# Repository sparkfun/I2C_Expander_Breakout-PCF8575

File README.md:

SparkFun I2C Expander Breakout - PCF8575
========================================

[*SparkFun I2C Expander Breakout - PCF8575 (BOB-08130)*](https://www.sparkfun.com/products/8130)

This great IC allows the user to expand up to 16 I/O using only two I/O for control! 
The PCF8575C is controlled through an I2C interface and features 16-bits of quasi-bidirectional input/output pins.

Repository Contents
-------------------

* **/Firmware** - Example code 
* **/Hardware** - Eagle design files (.brd, .sch)
* **/Production** - Production panel files (.brd)

Documentation
--------------
* **[SparkFun Fritzing repo](https://github.com/sparkfun/Fritzing_Parts)** - Fritzing diagrams for SparkFun products.
* **[SparkFun 3D Model repo](https://github.com/sparkfun/3D_Models)** - 3D models of SparkFun products. 

License Information
-------------------
This product is _**open source**_! 

The **hardware** is released under [Creative Commons ShareAlike 4.0 International](https://creativecommons.org/licenses/by-sa/4.0/).

The **code** is beerware; if you see me (or any other SparkFun employee) at the local, and you've found our code helpful, please buy us a round!

Please use, reuse, and modify these files as you see fit. Please maintain attribution to SparkFun Electronics and release anything derivative under the same license.

Distributed as-is; no warranty is given.

- Your friends at SparkFun.

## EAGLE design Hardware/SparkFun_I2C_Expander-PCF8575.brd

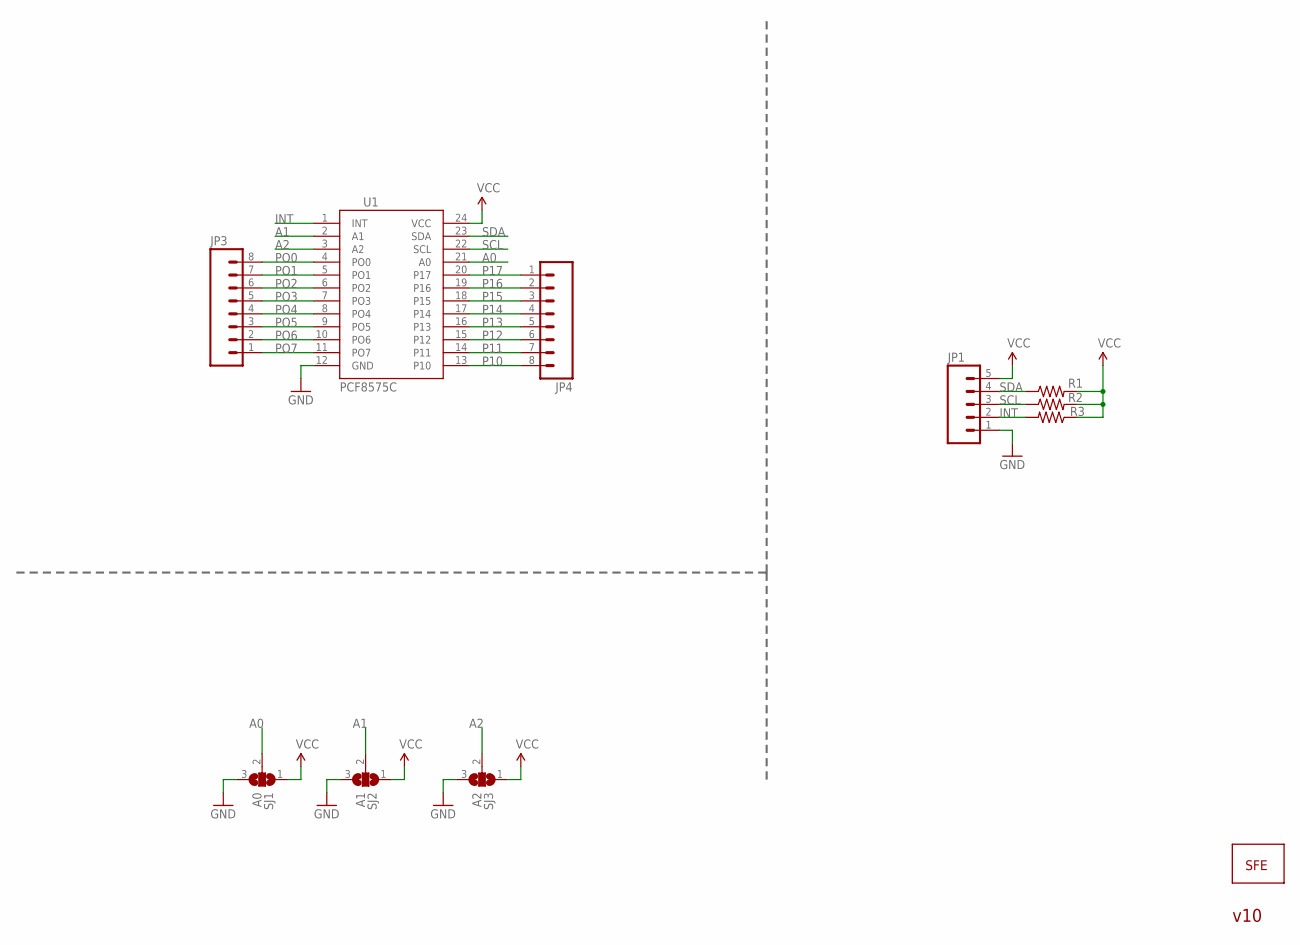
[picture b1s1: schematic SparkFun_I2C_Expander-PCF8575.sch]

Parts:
JP1: M05; 1X05
JP3, JP4: M08; 1X08
R1, R2, R3: RESISTOR0402; C0402
SJ1: A0; SJ_3
SJ2: A1; SJ_3
SJ3: A2; SJ_3
U1: PCF8575C; SO-24DW
U$2: LOGO-SFENEW; SFE-NEW-WEBLOGO

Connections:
A0: SJ1.2, U1.21 (A0)
A1: SJ2.2, U1.2 (A1)
A2: SJ3.2, U1.3 (A2)
GND: JP1.1, SJ1.3, SJ2.3, SJ3.3, U1.12 (GND)
INT: JP1.2, R3.2, U1.1 (INT)
P10: JP4.8, U1.13 (P10)
P11: JP4.7, U1.14 (P11)
P12: JP4.6, U1.15 (P12)
P13: JP4.5, U1.16 (P13)
P14: JP4.4, U1.17 (P14)
P15: JP4.3, U1.18 (P15)
P16: JP4.2, U1.19 (P16)
P17: JP4.1, U1.20 (P17)
PO0: JP3.8, U1.4 (PO0)
PO1: JP3.7, U1.5 (PO1)
PO2: JP3.6, U1.6 (PO2)
PO3: JP3.5, U1.7 (PO3)
PO4: JP3.4, U1.8 (PO4)
PO5: JP3.3, U1.9 (PO5)
PO6: JP3.2, U1.10 (PO6)
PO7: JP3.1, U1.11 (PO7)
SCL: JP1.3, R2.1, U1.22 (SCL)
SDA: JP1.4, R1.1, U1.23 (SDA)
VCC: JP1.5, R1.2, R2.2, R3.1, SJ1.1, SJ2.1, SJ3.1, U1.24 (VCC)

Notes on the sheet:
v10

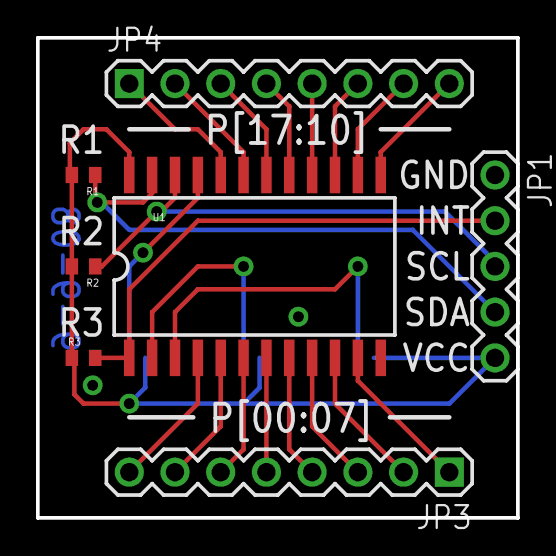
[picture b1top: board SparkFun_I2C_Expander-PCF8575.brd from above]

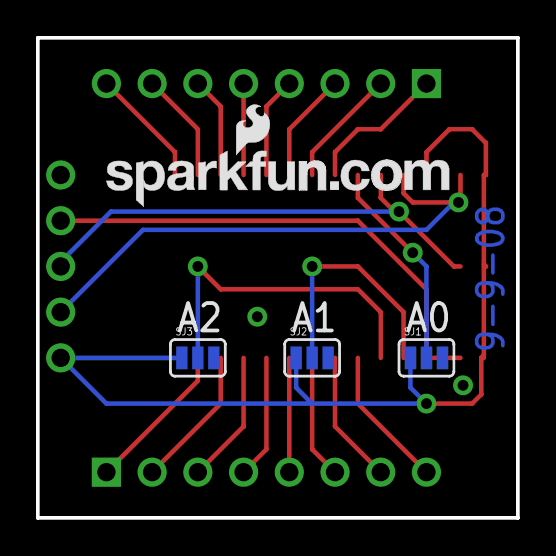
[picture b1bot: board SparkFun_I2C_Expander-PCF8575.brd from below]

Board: 2 copper layers, 26.7 x 26.7 mm, 11 parts (4 on the bottom side), 24 nets.

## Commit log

2015-05-06 Adding hardware files, example code, readme
